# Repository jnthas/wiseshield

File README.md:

# Clockwise Controller Boards Repository

This repository serves as the central hub for controller boards designed for the [Clockwise project](https://github.com/jnthas/clockwise).

## What is this repository for?

The goal is to maintain and share open hardware designs for various controller boards that can be used with Clockwise. These controller boards are the “brains” that drive the electronics in your Clockwise project.

## Philosophy

- **Modularity:** Support multiple MCUs (microcontroller units) to maximize flexibility.
- **DIY and Accessibility:** Offer designs that are easy for users to build at home, as well as options focused on small size and low cost.
- **Diversity:** Grow the ecosystem by adding boards for a range of microcontrollers, such as ESP32 variants, Raspberry Pi Pico, and more.

## Boards

### WiseShield-32

- The first controller board in this repository.
- Uses an ESP32 Dev Board as its MCU.
- Design focuses on maker-friendliness, available gerbers and source files.

## How to contribute

If you have an idea, improvement, or want to add your own controller board design, please open an issue or a pull request!

## License

This repository is under the MIT License. See the [LICENSE](LICENSE) file for details.

## Learn more

- Main Clockwise repository: [github.com/jnthas/clockwise](https://github.com/jnthas/clockwise)
- For questions and discussion, use the Issues section.

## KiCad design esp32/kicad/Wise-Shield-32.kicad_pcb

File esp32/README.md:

# WiseShield-32 Controller Board

WiseShield-32 is the first controller board developed for the [Clockwise project](https://github.com/jnthas/clockwise). It is designed for versatility, ease of assembly, and compatibility with popular display and peripheral modules.

## Overview

- **MCU**: ESP32 Dev Board (DOIT or compatible)
- **Purpose**: General-purpose, DIY-friendly board for driving various display and peripheral modules as part of the Clockwise ecosystem
- **Focus**: Maker-friendliness, modularity, and open-source design

## Repository Structure

- **gerbers/**: Production files ready for PCB manufacturing (Gerber files, drills, and Bill of Materials)
- **kicad/**: Complete schematic, PCB design files, 3D models, symbols, footprints, and renders (PNG, SVG)
    - Libraries folder contains custom symbols and footprints.
    - Placement folder contains component placement files.

### Key Files

- `gerbers/Wise-Shield-32-BOM.csv`: Full Bill of Materials with component reference
- `gerbers/Wise-Shield-32-*.gbr`: Individual Gerber layers for PCB fabrication
- `gerbers/Wise-Shield-32-iBom.html`: Interactive HTML BOM
- `kicad/Wise-Shield-32.kicad_sch`: Schematic (KiCad)
- `kicad/Wise-Shield-32.kicad_pcb`: Board layout (KiCad)
- `kicad/Wise-Shield-32-brd.png` and `kicad/Wise-Shield-32-brd.svg`: Board visualizations
- `kicad/libraries/`: Custom footprints, 3D models, and schematic symbols

## Features

- Compatible with standard ESP32 Dev Boards
- HUB75 and other display connector footprints available
- Designed for both experimental and permanent installations
- All files provided for at-home or commercial PCB assembly

## Getting Started

1. Clone the repository
2. Review schematic and BOM
3. Manufacture the PCB using the provided Gerber files, or edit the design using KiCad
4. Assemble and populate components as described in the BOM

## Assembly

This board can be assembled by hand, with through-hole and standard SMD (where applicable) components. See the BOM and placement files for specific guidance.

Check the Interactive BOM [here](gerbers/Wise-Shield-32-iBom.html)

## Schematic

## License

This project is licensed under the MIT License. See the [main repository](../../README.md) for details.

## About Clockwise

For details on the Clockwise project, usage examples, and broader ecosystem, visit: [github.com/jnthas/clockwise](https://github.com/jnthas/clockwise)

---

For questions or improvements, open an issue or submit a pull request!

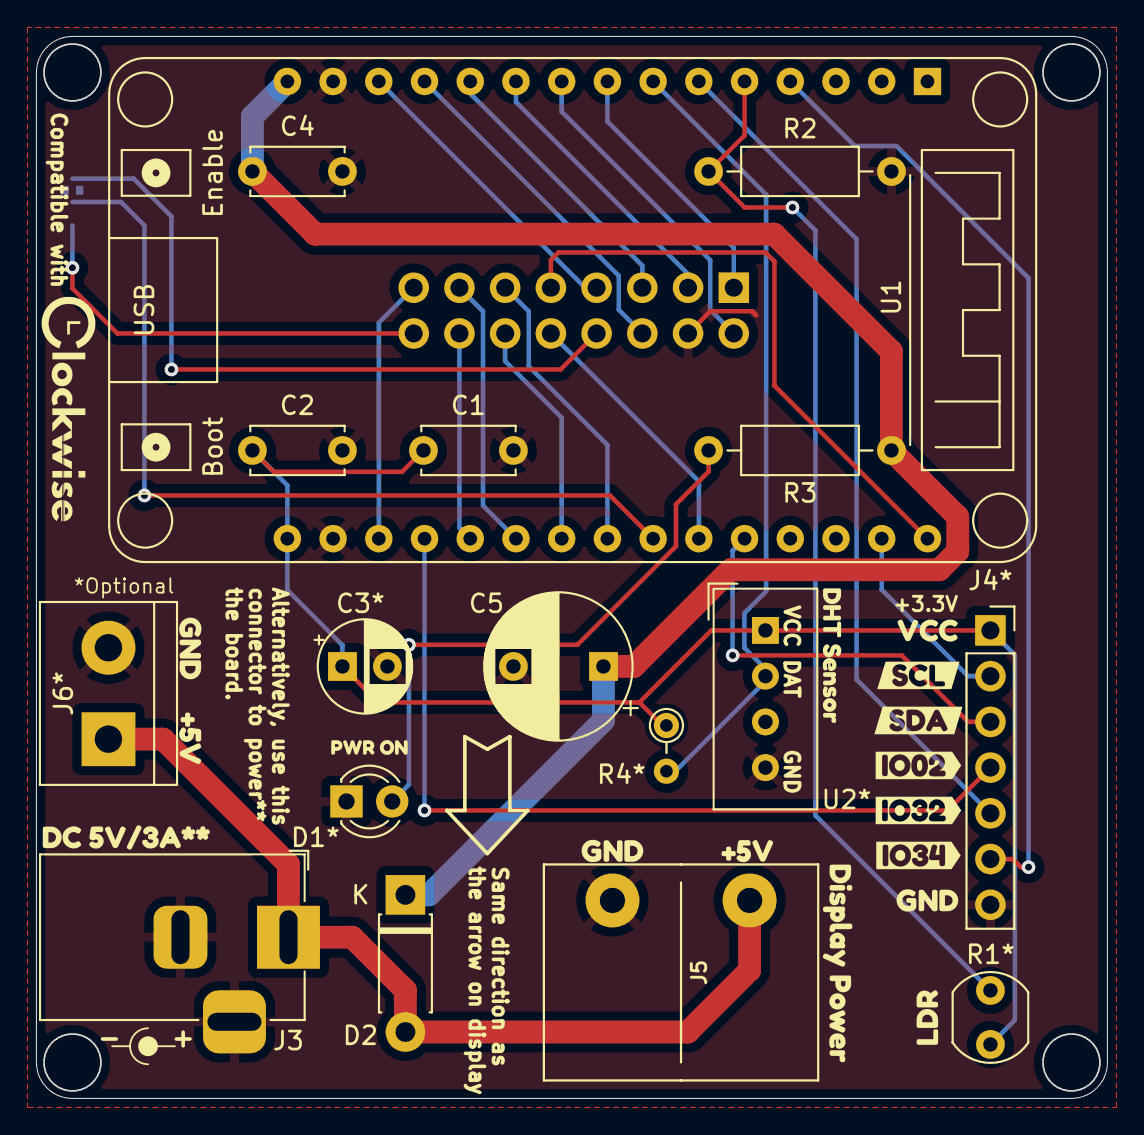
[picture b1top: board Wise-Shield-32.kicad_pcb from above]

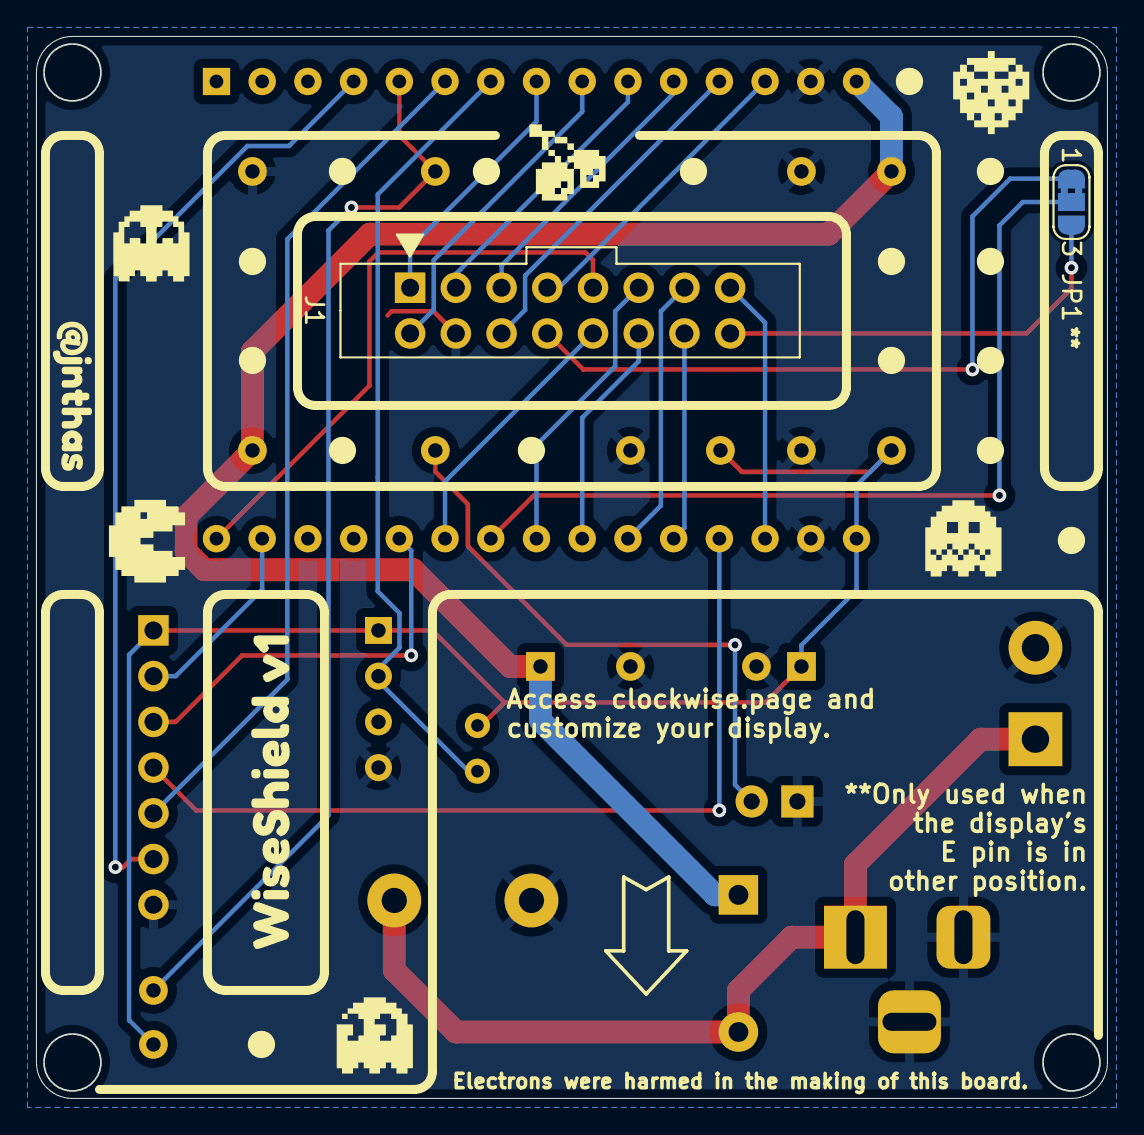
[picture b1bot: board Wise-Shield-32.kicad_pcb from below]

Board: 2 copper layers, 59.5 x 59.0 mm, 37 parts (4 on the bottom side), 28 nets.

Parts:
C1, C2: 100nF; C_Disc_D5.0mm_W2.5mm_P5.00mm
C3*: 100uF; CP_Radial_D5.0mm_P2.50mm
C4: 1uF; C_Disc_D5.0mm_W2.5mm_P5.00mm
C5: 470uF; CP_Radial_D8.0mm_P5.00mm
D1*: LED; LED_D3.0mm
D2: 1N5819; D_DO-41_SOD81_P7.62mm_Horizontal
J1: HUB75_Connector_02x08; HUB75_Socket_2x8_P2.54mm_Vertical
J3: Power Input; BarrelJack_Horizontal
J4*: Expansion Header; PinSocket_1x07_P2.54mm_Vertical
J5: Display Power; KF7.62_2P
J6*: Power Input; TerminalBlock_bornier-2_P5.08mm
JP1: PinE; SolderJumper-3_P1.3mm_Bridged2Bar12_RoundedPad1.0x1.5mm_Num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
R1*: A9050; R_LDR_5.0x4.1mm_P3mm_Vertical
R2: 10K; R_Axial_DIN0207_L6.3mm_D2.5mm_P10.16mm_Horizontal
R3: 1K; R_Axial_DIN0207_L6.3mm_D2.5mm_P10.16mm_Horizontal
R4*: 10K; R_Axial_DIN0204_L3.6mm_D1.6mm_P2.54mm_Vertical
U1: ESP32_DevKit_V1_DOIT; esp32_devkit_v1_doit
U2*: DHT11; Aosong_DHT11_5.5x12.0_P2.54mm
kibuzzard-679FD3E6: G***; kibuzzard-679FD3E6
kibuzzard-6791A0E6: G***; kibuzzard-6791A0E6
kibuzzard-6792CDDD: G***; kibuzzard-6792CDDD
kibuzzard-6792CDE8: G***; kibuzzard-6792CDE8
kibuzzard-6792CDEE: G***; kibuzzard-6792CDEE
kibuzzard-6792CDF2: G***; kibuzzard-6792CDF2
kibuzzard-6792CDF7: G***; kibuzzard-6792CDF7
kibuzzard-6792CDFD: G***; kibuzzard-6792CDFD
kibuzzard-67926B2D: G***; kibuzzard-67926B2D
kibuzzard-67964EF4: G***; kibuzzard-67964EF4
kibuzzard-679260A2, kibuzzard-679260A2-2: G***; kibuzzard-679260A2
kibuzzard-679260BA, kibuzzard-679260BA-2: G***; kibuzzard-679260BA
kibuzzard-679263B5: G***; kibuzzard-679263B5
kibuzzard-679265D3: G***; kibuzzard-679265D3
kibuzzard-6796368B: G***; kibuzzard-6796368B
kibuzzard-67963938: G***; kibuzzard-67963938

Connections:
+3.3V: C1.1, C2.1, C3*.1, J4*.1, R1*.1, R4*.1, U1.16 (3V3), U2*.1 (VDD)
+5VA: D2.2 (A), J3.1, J5.1, J6*.1
GNDREF: C1.2, C2.2, C3*.2, C4.2, C5.2, D1*.1 (K), J1.GND (Pin_4), J3.2, J3.3, J4*.7, J5.2, J6*.2, R2.2, U1.14 (GND), U1.17 (GND), U2*.4 (GND)
IO02: J4*.4, U1.19 (IO2)
IO04: J1.LAT (Pin_14), U1.20 (IO4)
IO05: J1.C (Pin_11), U1.23 (IO5)
IO12: J1.G2 (Pin_6), U1.12 (IO12)
IO13: J1.B2 (Pin_7), U1.13 (IO13)
IO14: J1.R2 (Pin_5), U1.11 (IO14)
IO15: J1.OE (Pin_15), U1.18 (IO15)
IO16: J1.CLK (Pin_13), U1.21 (IO16)
IO17: J1.D (Pin_12), U1.22 (IO17)
IO18: JP1.2 (C), U1.24 (IO18)
IO19: J1.B (Pin_10), U1.25 (IO19)
IO23: J1.A (Pin_9), U1.30 (IO23)
IO25: J1.R1 (Pin_1), U1.8 (IO25)
IO26: J1.G1 (Pin_2), U1.9 (IO26)
IO27: J1.B1 (Pin_3), U1.10 (IO27)
IO32: J4*.5, U1.6 (IO32)
IO33: R4*.2, U1.7 (IO33), U2*.2 (DATA)
IO34: J4*.6, U1.4 (IO34)
IO35: R1*.2, R2.1, U1.5 (IO35)
unnamed: D1*.2 (A), R3.2
unnamed: J1.E (Pin_8), JP1.1 (A)
unnamed: J1.G/E (Pin_16), JP1.3 (B)
PWR_ON: C4.1, C5.1, D2.1 (K), R3.1, U1.15 (VIN)
SCL: J4*.2, U1.29 (IO22)
SDA: J4*.3, U1.26 (IO21)

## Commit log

2025-09-09 adds wiseshield-32 board project
2025-09-13 Added schematic and iBom

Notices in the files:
esp32/kicad/Wise-Shield-32.kicad_pcb:
https://creativecommons.org/licenses/by/4.0
License: CC BY 4.0
